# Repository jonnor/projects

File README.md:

Misc projects. Electronics, physical/mechanical, software.
3d-models, schematics, scripts.

# Introspectable computing

* [Agree.js](https://agreejs.org)
* [Finito](https://finitosm.org)

## Flow-based-programming

* [MicroFlo](https://microflo.org)
* [imgflo](https://imgflo.org)
* [MsgFlo](https://msgflo.org)
* [fbp-spec](https://github.com/flowbased/fbp-spec)
* [flowtrace](https://github.com/flowbased/flowtrace)

# Open hardware

* [TapeCore / TapeXY](./tapecore), an laserengraver and CNC motion platform
* [Idda](./idda-knitting-machine), a reverse-engineered ciruclar knitting machine.

# Digital fabrication tools

* [FreeCAD](./freecad) single-source /continious-integration
* [doctags](./doctags)

# Other interests

* [Bioplastic](./bioplastic)
* [Piezoelectricity](./piezo)
* [Automation](./automation)

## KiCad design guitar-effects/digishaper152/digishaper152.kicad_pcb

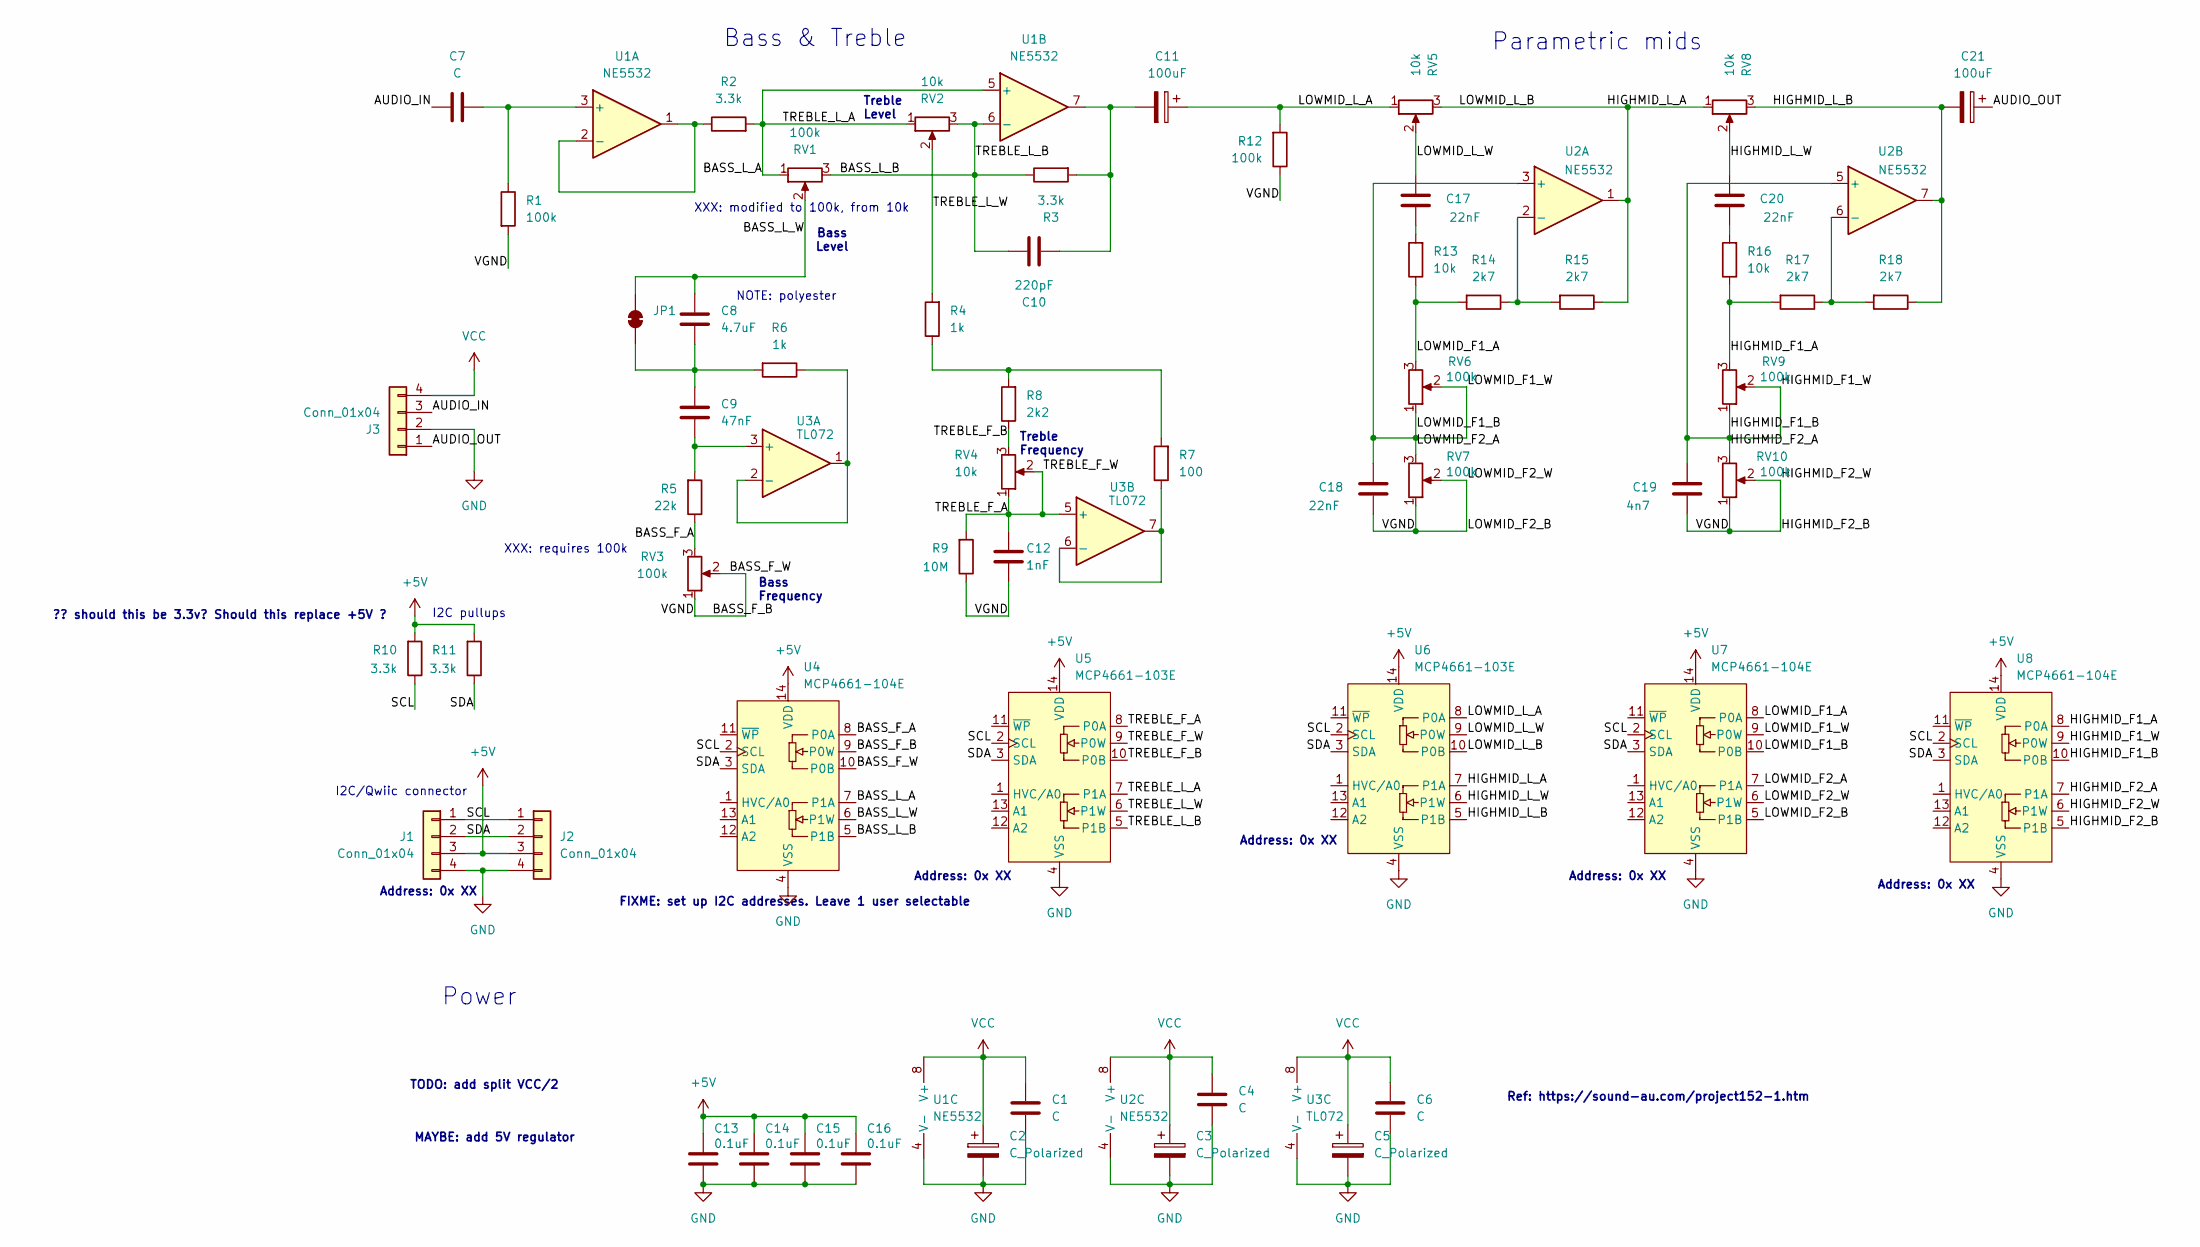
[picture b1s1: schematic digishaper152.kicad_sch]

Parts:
C1, C4, C6, C7: C; C_0805_2012Metric
C2, C3, C5: C_Polarized; C_0805_2012Metric
C8: 4.7uF; C_0805_2012Metric
C9: 47nF; C_0805_2012Metric
C10: 220pF; C_0805_2012Metric
C11, C21: 100uF; C_0805_2012Metric
C12: 1nF; C_0805_2012Metric
C13, C14, C15, C16: 0.1uF; C_0805_2012Metric
C17, C18, C20: 22nF; C_0805_2012Metric
C19: 4n7; C_0805_2012Metric
J1, J2: Conn_01x04; JST_SH_SM04B-SRSS-TB_1x04-1MP_P1.00mm_Horizontal
J3: Conn_01x04; PinHeader_1x04_P2.54mm_Vertical
JP1: SolderJumper_2_Bridged; SolderJumper-2_P1.3mm_Bridged_RoundedPad1.0x1.5mm
R1, R12: 100k; R_0805_2012Metric
R2, R3, R10, R11: 3.3k; R_0805_2012Metric
R4, R6: 1k; R_0805_2012Metric
R5: 22k; R_0805_2012Metric
R7: 100; R_0805_2012Metric
R8: 2k2; R_0805_2012Metric
R9: 10M; R_0805_2012Metric
R13, R16: 10k; R_0805_2012Metric
R14, R15, R17, R18: 2k7; R_0805_2012Metric
RV1, RV3, RV6, RV7, RV9, RV10: 100k; PinHeader_1x03_P1.27mm_Vertical
RV2, RV4, RV5, RV8: 10k; PinHeader_1x03_P1.27mm_Vertical
U1, U2: NE5532; SOIC-8_3.9x4.9mm_P1.27mm
U3: TL072; SOIC-8_3.9x4.9mm_P1.27mm
U4, U7, U8: MCP4661-104E; TSSOP-14_4.4x5mm_P0.65mm
U5, U6: MCP4661-103E; TSSOP-14_4.4x5mm_P0.65mm

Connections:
+5V: C13.1, C14.1, C15.1, C16.1, J1.3, J2.3, R10.2, R11.2, U4.14 (VDD), U5.14 (VDD), U6.14 (VDD), U7.14 (VDD), U8.14 (VDD)
/AUDIO_IN: C7.1, J3.3
/AUDIO_OUT: C21.1, J3.1
/BASS_F_A: R5.1, RV3.3, U4.8 (P0A)
/BASS_F_B: C12.1, C18.2, C19.2, R1.2, R9.1, R12.1, RV3.1, RV3.2, RV7.1, RV7.2, RV10.1, RV10.2, U4.9 (P0W), U4.10 (P0B), U7.5 (P1B), U7.6 (P1W), U8.5 (P1B), U8.6 (P1W)
/BASS_L_A: R2.2, RV1.1, RV2.1, U1.5 (+), U4.7 (P1A), U5.7 (P1A)
/BASS_L_B: C10.2, R3.1, RV1.3, RV2.3, U1.6 (-), U4.5 (P1B), U5.5 (P1B)
/BASS_L_W: C8.2, JP1.2 (B), RV1.2, U4.6 (P1W)
/HIGHMID_F1_A: R16.1, R17.2, RV9.3, U8.8 (P0A)
/HIGHMID_F1_B: C19.1, RV9.1, RV9.2, RV10.3, U2.5 (+), U8.7 (P1A), U8.9 (P0W), U8.10 (P0B)
/HIGHMID_L_A: R15.1, RV5.3, RV8.1, U2.1, U6.7 (P1A), U6.10 (P0B)
/HIGHMID_L_B: C21.2, R18.1, RV8.3, U2.7, U6.5 (P1B)
/HIGHMID_L_W: C20.1, RV8.2, U6.6 (P1W)
/LOWMID_F1_A: R13.1, R14.2, RV6.3, U7.8 (P0A)
/LOWMID_F1_B: C18.1, RV6.1, RV6.2, RV7.3, U2.3 (+), U7.7 (P1A), U7.9 (P0W), U7.10 (P0B)
/LOWMID_L_A: C11.1, R12.2, RV5.1, U6.8 (P0A)
/LOWMID_L_W: C17.1, RV5.2, U6.9 (P0W)
/SCL: J1.1, J2.1, R10.1, U4.2 (SCL), U5.2 (SCL), U6.2 (SCL), U7.2 (SCL), U8.2 (SCL)
/SDA: J1.2, J2.2, R11.1, U4.3 (SDA), U5.3 (SDA), U6.3 (SDA), U7.3 (SDA), U8.3 (SDA)
/TREBLE_F_A: C12.2, R9.2, RV4.1, RV4.2, U3.5 (+), U5.8 (P0A), U5.9 (P0W)
/TREBLE_F_B: R8.1, RV4.3, U5.10 (P0B)
/TREBLE_L_W: R4.2, RV2.2, U5.6 (P1W)
GND: C1.2, C2.2, C3.2, C4.2, C5.2, C6.2, C13.2, C14.2, C15.2, C16.2, J1.4, J2.4, J3.2, U1.4 (V-), U2.4 (V-), U3.4 (V-), U4.4 (VSS), U5.4 (VSS), U6.4 (VSS), U7.4 (VSS), U8.4 (VSS)
unnamed: C10.1, C11.2, R3.2, U1.7
unnamed: C17.2, R13.2
unnamed: C20.2, R16.2
unnamed: C8.1, C9.2, JP1.1 (A), R6.2
unnamed: R4.1, R7.2, R8.2
unnamed: C7.2, R1.1, U1.3 (+)
unnamed: R2.1, U1.1, U1.2 (-)
unnamed: R14.1, R15.2, U2.2 (-)
unnamed: R17.1, R18.2, U2.6 (-)
unnamed: C9.1, R5.2, U3.3 (+)
unnamed: R6.1, U3.1, U3.2 (-)
unnamed: R7.1, U3.6 (-), U3.7
VCC: C1.1, C2.1, C3.1, C4.1, C5.1, C6.1, J3.4, U1.8 (V+), U2.8 (V+), U3.8 (V+)

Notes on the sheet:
Bass & Treble
Address: 0x XX
MAYBE: add 5V regulator
XXX: modified to 100k, from 10k
Treble Level
FIXME: set up I2C addresses. Leave 1 user selectable
Parametric mids
Power
I2C pullups
XXX: requires 100k
Ref: https://sound-au.com/project152-1.htm
I2C/Qwiic connector
TODO: add split VCC/2
Bass Frequency
?? should this be 3.3v? Should this replace +5V ?
Bass Level
Treble Frequency
NOTE: polyester

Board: 2 copper layers, 61 parts (0 on the bottom side), 36 nets, no tracks yet.

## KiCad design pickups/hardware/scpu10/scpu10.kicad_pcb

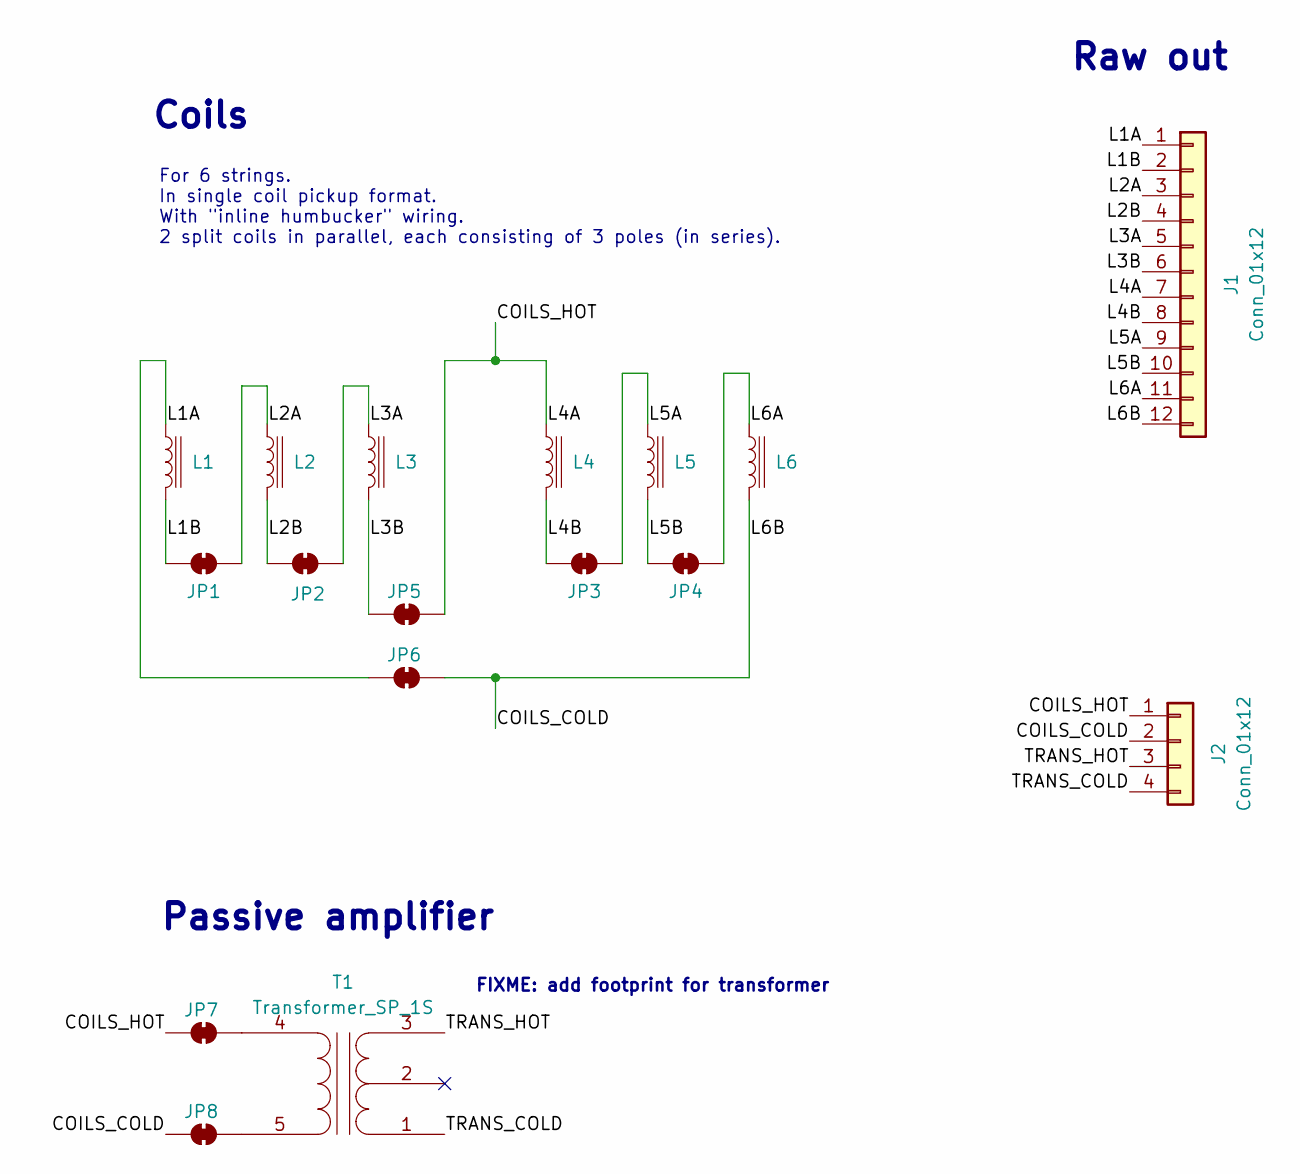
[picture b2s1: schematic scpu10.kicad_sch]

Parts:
J1: Conn_01x12; PinHeader_1x12_P2.54mm_Vertical
J2: Conn_01x12; PinHeader_1x04_P2.54mm_Vertical
JP1, JP2, JP3, JP4, JP5, JP6, JP7, JP8: SolderJumper_2_Bridged; SolderJumper-2_P1.3mm_Bridged_RoundedPad1.0x1.5mm
L1, L2, L3, L4, L5, L6: L_Iron; L_Radial_D8.7mm_P5.00mm_Fastron_07HCP
T1: Transformer_SP_1S

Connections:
/COILS_COLD: J1.12, J2.2, JP6.2 (B), JP8.1 (A), L6.2
/COILS_HOT: J1.7, J2.1, JP5.2 (B), JP7.1 (A), L4.1
/L1A: J1.1, JP6.1 (A), L1.1
/L1B: J1.2, JP1.1 (A), L1.2
/L2A: J1.3, JP1.2 (B), L2.1
/L2B: J1.4, JP2.1 (A), L2.2
/L3A: J1.5, JP2.2 (B), L3.1
/L3B: J1.6, JP5.1 (A), L3.2
/L4B: J1.8, JP3.1 (A), L4.2
/L5A: J1.9, JP3.2 (B), L5.1
/L5B: J1.10, JP4.1 (A), L5.2
/L6A: J1.11, JP4.2 (B), L6.1
/TRANS_COLD: J2.4, T1.1 (PR1)
/TRANS_HOT: J2.3, T1.3 (PR2)
unnamed: JP7.2 (B), T1.4 (S1)
unnamed: JP8.2 (B), T1.5 (S2)

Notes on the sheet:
For 6 strings. In single coil pickup format. With "inline humbucker" wiring. 2 split coils in parallel, each consisting of 3 poles (in series).
Raw out
FIXME: add footprint for transformer
Passive amplifier
Coils

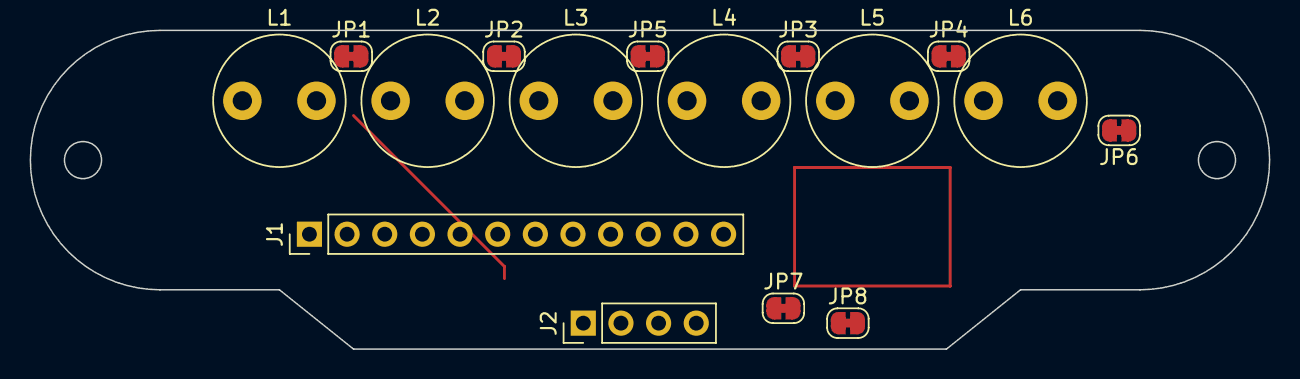
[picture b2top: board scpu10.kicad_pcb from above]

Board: 2 copper layers, 83.6 x 21.5 mm, 16 parts (0 on the bottom side), 12 nets.

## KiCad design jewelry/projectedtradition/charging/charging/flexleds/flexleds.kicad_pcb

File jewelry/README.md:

# Resin-based

Etsy.com. [Lots](https://www.etsy.com/no-en/search?q=epoxy+jewelry&explicit=1&page=3) of amazing looking products. Mostly rings,pendants.
Pure resin or resin+wood. 200-400 NOK. Sometimes glow-in-the-dark.
Resin 'stone' with wood base, silver ring inlay. 700-800 NOK.

Maybe silver + resin cast rings has good opportunity? Not found, might be able to push price up.

# Silver-based

Oxididation. Electroetching with laser-engraved masks?

# Gemstones

Small oval gemstones, 10-20 mm. [1](https://www.gemselect.com/group/gemselect.php?a=0&base_shape=Oval,Pear,Round&min_l=10.00&max_l=20.00&min_w=10.00&max_w=20.00&styles=Cabochon%27,%27Plain-Cut&price_asc=1&page=1)

# Rechargable

Power board for wearable or other battery powered electronics.

- Integrated charger for LIR coincell batteries.
- Integrated touch-controller for power on/off.
- Charging via USB 4pin magnetic cable.
- Fits LIR16xx,LIR20xx and LIR24xx directly.
- Board fits within 20 mm diameter, 2 mm height

## Top PCB

Projected. 3030 with touch on back

- 3030 LED on top
- 4 pin connector 1.0mm pitch
- Touch plate on the bottom.
Rounded rectangle
Keep below 12mm diameter?

## Tests

Tested charging. Seems to work as-intended.
Tested reverse-polarity protection. Works.

Tested attaching battery.
The solder joints may come out on lower side of PCB.
Can interfere with mounting. Should adapt bottom plate to accomodate.

Tested attaching cable for top PCB.
The purchased FFC just melts the backing material instantly. FAIL. Should use a Kapton-based instead.
It was possible to remove the thick spacers, add a Kapton+HT polyester layers, and melt away the plastic, and then solder this on.
However it remains quite tricky to do.
A jig to help with alignment would help.
Proper light and flux would also help.
Longer traces and wider pitch should be considered for next revision.

Need approx 45 mm FPC cable to get to top of dome.

Tested having an external copper piece for touch.
Using a resing printed dome, approx 1mm thick. Touching from outside.
With a single wire and 47 pF, did not react.
With alu foil of approx 10x10 mm and 47 pF, did not react.
With alu foil of approx 10x0 mm and C2 removed, reacts easily.
Need no or a small value for C2. Test 1 pF?

## TODO

Projected PCB rev 1 testing

- Add flat part to model dome, for LED PCB
- Assemble a complete piece
- Make stand functional
Thickness and tolerances on connector needs fixing
Orientation of cable outlet should be rotated 90degrees
- Test connector and charging, reliability/ease-of-use
- Try plugging the chargint through-hole.
See if one can use just SMT pads. Frees up a lot of board space for components.

Projected PCB rev 2 send

- Make LED/touch PCB for top.
Connections power,GND,touch
Include into main PCB project?
- Probably, use SMT pads for charging
- Maybe switch to 1.27mm solder tab FPC

Projected PCB rev 2 testing

- Make jig for holding PCBs and FPC cable for soldering
- Complete assembly. 3 units

## Next version

APA102 2020 strip
- ish 4 mm wide
- 4 pin connector. On LED side?
- space for 0603 capacitor
- at least 60mm length, for Atlantis earcuffs
- connector for chaining
- exposed pads between LEDs for ability to cut-to-length
- as close as possible. Ex 3 mm spacing 
can skip in software if not all are used

Insp. https://www.pcbway.com/project/shareproject/SK9822_APA102_LED_Breakout_board_array.html

Merge with "projected"

TODO:
- Test APA102 2020 / SK9822 at 3.6V power
Has been reported working ok.
https://forum.pjrc.com/threads/30020-Teensy-APA102-POV-Poi-Pixel-Poi-Build-Tutorial?p=84907&viewfull=1#post84907
- Integrate a microcontroller. ATtiny1616 ?
- Do touch control in microcontroller
- Support USB reconfiguration/programming over magnet connector
- Support APA102 style LEDs.
Put 1 on PCB, then to connector
VCC,GND,clk,data

## Notes
On two different magnetic USB cables, of same format. 4 pins
5V at tip, GND at base towards cable. Same.
However the magnets were oriented the other direction. South/North

## 2 pin inline

2 pin magnetic pogo pins
Many different sizes. Pin distances from 2 to 4mm
14 mm total length
https://www.aliexpress.com/item/4001134405952.html
https://www.aliexpress.com/item/33009498882.html
https://www.cletk.com/connector/high-class-2-pin-magnetic-charging-cable-for-smart-watch
https://www.aliexpress.com/item/4001065386444.html
https://www.aliexpress.com/item/4000209947392.html
https://www.aliexpress.com/item/4001149140826.html
https://www.aliexpress.com/item/1005002013444317.html

## Rotary magnetic

About 7.5 to 8.5 mm diameter

https://www.aliexpress.com/item/1005002177757313.html
https://www.aliexpress.com/item/4001135270257.html
https://www.aliexpress.com/item/4000109101082.html
https://www.aliexpress.com/item/4000109004581.html

## Parts 

Diode Shottky SOD323
https://www.digikey.com/en/products/filter/diodes-rectifiers-single/280?s=N4IgjCBcpgbFoDGUBmBDANgZwKYBoQB7KAbRAGYBOAJgBZ4DaAGJuiRlsSiAXQIAcALlBABlQQCcAlgDsA5iAC%2BBSvGghkkdNnxFSIZk3IB2ABwg%2BIISPHT5SggFpqCDVEkBXXcUhkArCAqFgLCkCAOII4B6prauAQ%2BZC6W1mFKyiBqoFIAJiKOYEzsVqHhBACOggCeIoWBINX8OCJoWMiKikA

PMOS SOT-223
https://www.digikey.com/en/products/filter/transistors-fets-mosfets-single/278?s=N4IgjCBcoGwAwyqAxlAZgQwDYGcCmANCAPZQDaIAzABwCsYclIAukQA4AuUIAyhwE4BLAHYBzEAF8iMMACYkIVJEy5CJcuBi0YsuCCKzDYGAE59IWTQAsc87NoB2KzCYHqT2lfOmwn7ybAHRGkTWV9zahsrWgjHLXMGOGiHBLgk2mpUpOp5IkSraky8uAyTM2LaUIg8hhgHGJrPMISrBDhq8BtaSoTHOAdXcD66BJNKJJSDNOodO0ofYIsHeuMWdi5IXgERcSlwWQCFJRV8IlJIClbaSiDzK5vJkFb2kwankqt6u4-ltZBObh8IRiSREAC08mgiigAgArmpzhQ3mZWP8NiBJHtEFDBAATbhghgdAGbcwARw4AE9uAxzFS2HhuBgcKgJBIgA

LIR1620 / LIR1632
LIR2032
LIR2450
Rainpro @ Aliexpress

LED driver. Linear regulator, low-dropout

BCR430U

## JST SUR 0.8 mm pitch connector

SM04B-SRSS-TB(LF)(SN) 
https://www.digikey.no/product-detail/no/jst-sales-america-inc/SM04B-SRSS-TB-LF-SN/455-1804-6-ND/1963508

There are now SUR connectors from JST also.
They have 0.8 mm pitch, and 1 mm height

https://www.digikey.com/en/products/detail/jst-sales-america-inc/SM04B-SURS-TF-LF-SN/7230518
https://www.digikey.com/en/products/detail/jst-sales-america-inc/A04SUR04SUR32W102A/9947438

https://www.aliexpress.com/item/32835280612.html?spm=a2g0o.cart.0.0.44853c0032a3Bk&mp=1
https://www.aliexpress.com/item/32834920580.html?spm=a2g0o.cart.0.0.44853c0032a3Bk&mp=1
https://www.aliexpress.com/item/4001089049756.html?spm=a2g0o.cart.0.0.44853c0032a3Bk&mp=1
https://www.aliexpress.com/item/4001089049756.html?spm=a2g0o.cart.0.0.44853c0032a3Bk&mp=1

FPC connector
https://www.digikey.com/en/products/detail/te-connectivity-amp-connectors/1734839-5/1860461

BCR430U

# Watch
Watch case 42 mm 43mm 
For movement ST36 ETA6497 ETA6498 P212
transparent back

https://www.aliexpress.com/item/4000229421123.html
https://www.aliexpress.com/item/4000689159663.html
https://www.aliexpress.com/item/32907052343.html

# Integrated electronics

## Structures

* Necklace, 2 parts on front connected with a tube. LED (and switch?) in one, battery in other.
* Pendant small. Eg with lit gemstone. LED and switch IC PCB underneath gemstone. Battery in/on clasp. 
* Pendant big. All electronics, incl battery, in pendant.

## Tested

Using bent copper wires on PCB for coincell battery holder.
GND as wire loop lying on PCB, VBAT as a loop standing out from board, that coincell slides underneath. Works nicely.
A jig could help bending correct wires before placing.

## Lights in motion

Animation ideas

* Subtle glow
* Glitter/sparkle. Random high-intensity bursts, alternating positions
* Together<->apart / center<->sides. 
* Swipe across. Random triggered, varying intensity
* Tick-tock. Move back/forward in a way that suggests clock motion

## Interactivity

* "touch me". Touch. Proximity. Gestures. Capacitive sensing.
* "move me". Motion. Angle. Accelerometer
* "I hear you". Sound. Music, wearer talking. Microphone.
* "I feel you". Body state. Temperature, breathing, heartbeat.
* "get close to me". Distance

Modulate intensity using touch proximity?

Accelerometers are available with `<10uA` consumption in low power mode.
I2C communication and configurable interrupts. Ex: LIS3DE, MMA8653FC 

# Learnings

Minimum hole size in cardboard. Vector: 0.5mm

# Rev2

* Total size `<40mm` diam, `<15 mm` height. Domed top. PCB 20mm diam, `<3mm` component height.
* LiPo battery, integrated charger. LIR2450-LIR2016
* Pogopin connector for charging
* TPP223 touch controller
* 3030 or 3535 white LED. Low-profile, 1mm. Low voltage? 3V
* LED constant-current driver

0.6mm PCB is OK priced on PCBWay. 0.4 and 0.2mm twice the price.
10mA on time.

FPC connector.
https://www.digikey.com/products/en/connectors-interconnects/ffc-fpc-flat-flexible-connectors/399?FV=fff40016%2Cfff80421%2C1600018%2C1600006%2C1b4c0008%2Cffe0018f%2Cfffc0017%2Cfffc0384&quantity=20&ColumnSort=1000011&page=2&stock=1&nstock=1&pageSize=25

100mAh, 10uA => 1 year.

LEDs

https://www.digikey.com/products/en/optoelectronics/led-lighting-white/124?FV=7%7C2%2C37%7C421162%2C319%7C133405%2C319%7C134015%2C319%7C134067%2C319%7C134280%2C319%7C134430%2C319%7C134479%2C319%7C134532%2C319%7C134768%2C319%7C135281%2C319%7C135361%2C319%7C135451%2C319%7C135630%2C319%7C135739%2C319%7C136170%2C319%7C136604%2C319%7C136643%2C319%7C136960%2C319%7C137263%2C319%7C137391%2C319%7C202627%2C319%7C202630%2C1500%7C4992%2C1500%7C5027%2C1500%7C5068%2C1500%7C5221%2C1500%7C5295%2C1500%7C5576%2C1500%7C5588%2C1500%7C5744%2C1500%7C5802%2C1500%7C5803%2C1500%7C5812%2C1500%7C5916%2C1500%7C5964%2C1500%7C6031%2C1500%7C6094%2C1500%7C6506%2C-8%7C124%2C1291%7C182983%2C1291%7C193429&quantity=10&ColumnSort=1000011&page=2&stock=1&nstock=1&pageSize=25

# TODO

* Make bottom PCB.
* Make LED PCB. Touch sensor electrode also?

Dock

* Fabricate a PCB for dock
* Make docking station mechanics

Later

* Move to separate repository

## USB DFU

USB DFU on STM32L432 and STM32L433
not conforming to spec?
https://community.st.com/s/question/0D50X00009XkfyUSAR/usb-dfu-on-stm32l432-and-stm32l433
Issue seems fixed in latest st-util?
https://sourceforge.net/p/dfu-util/tickets/40/

User-mode bootloader
https://github.com/nichtgedacht/L433CCTx-bootloader

# Ideas

Practical sizes

* Test a CR coincell holder inline with the PCB instead of on the back.
U-shape opening on one side. Wires on each side for GND/VBAT.
Reduces thickness by board+component height, approx 3 mm.
* Test using silver chains as conductor to battery.
Challenge: Has to be safe to have them touching, avoid shorts.
Current limiter. Active, passive resistor.

Consumer friendliness

* Ensure easy to put in battery correctly.
* Ensure that putting battery incorrectly does not cause damage?
* Maybe allow to adjust brightness. Touch-and-hold during startup?

Capacitive touch on/off

* Test have a hole/slit in housing, where a metallic piece/wire rests as the electrode.
Jewelry connected to GND.
* Test having a wire antenna sticking out towards front of rosebud.
With high sensitivity, can one switch using a gesture?

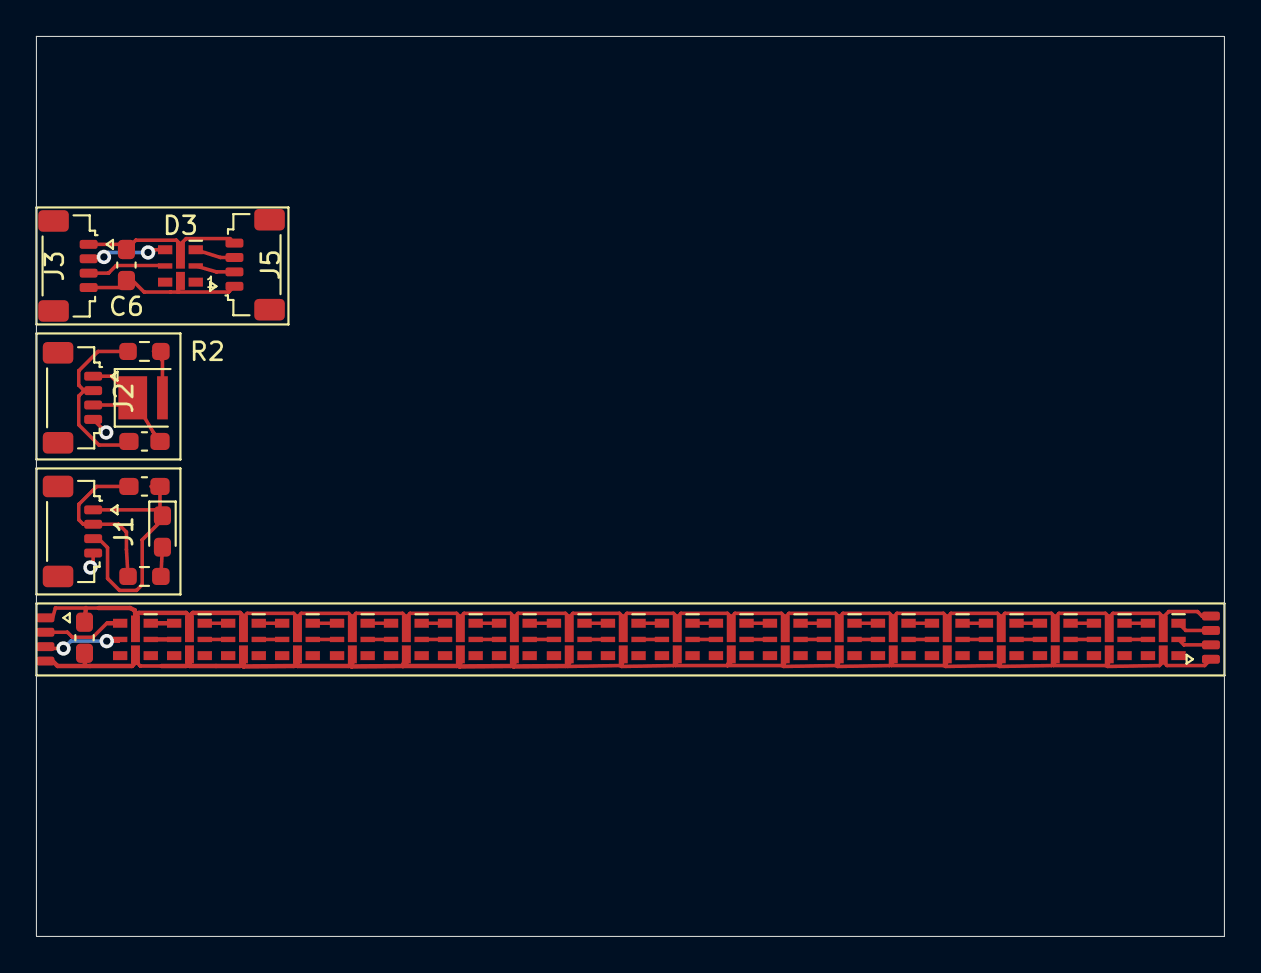
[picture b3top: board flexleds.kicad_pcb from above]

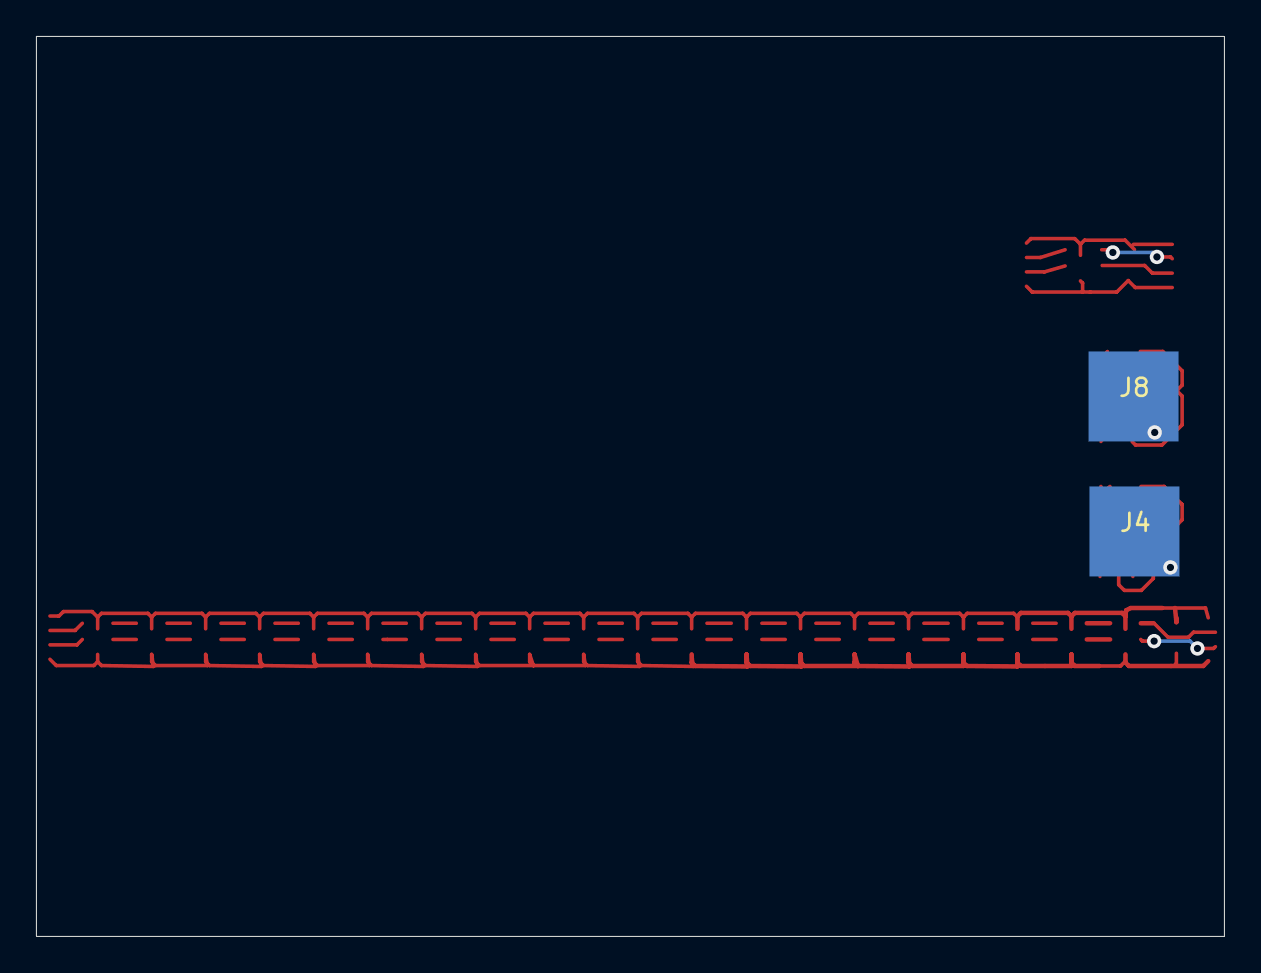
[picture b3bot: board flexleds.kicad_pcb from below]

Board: 2 copper layers, 66.0 x 50.0 mm, 37 parts (2 on the bottom side), 56 nets.

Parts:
C1, C3, C6, C7: C; C_0603_1608Metric_Pad1.08x0.95mm_HandSolder
D1: LED; LED_0603_1608Metric_Pad1.05x0.95mm_HandSolder
D2: LED; LED_Cree-J3030
D3, D4, D5, D6, D7, D8, D9, D10, D11, D12, D13, D14, D15, D16, D17, D18, D19, D20, D21, D22, D23: APA102-2020; LED-APA102-2020-midpower
J1, J2, J3, J5: Conn_01x04; JST_SUR_SM04B-SURS-TF_1x04-1MP_P0.80mm_Horizontal
J4, J8: Conn_01x01; touchpad
J6, J7: Conn_01x04; JST_SUR_SM04B-SURS-TF_1x04-1MP_P0.80mm_Horizontal_cut
R1, R2: R; R_0603_1608Metric_Pad0.98x0.95mm_HandSolder

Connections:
/0603_led: C1.1, J1.2, R1.1
/0603_touch: J1.4, J4.1
/3030_led: C3.1, J2.2, R2.1
/3030_touch: J2.4, J8.1
GND: C3.2, C6.2, C7.2, D2.1, D3.6, D4.6, D5.6, D6.6, D7.6, D8.6, D9.6, D10.6, D11.6, D12.6, D13.6, D14.6, D15.6, D16.6, D17.6, D18.6, D19.6, D20.6, D21.6, D22.6, D23.6, J2.1, J2.3, J3.1, J5.4, J6.1, J7.4
unnamed: C1.2, D1.1, J1.1, J1.3
unnamed: C6.1, D3.1, J3.4, J5.1
unnamed: C7.1, D4.1, D5.1, D6.1, D7.1, D8.1, D9.1, D10.1, D11.1, D12.1, D13.1, D14.1, D15.1, D16.1, D17.1, D18.1, D19.1, D20.1, D21.1, D22.1, D23.1, J6.4, J7.1
unnamed: D1.2, R1.2
unnamed: D2.2, R2.2
unnamed: D3.2, J5.2
unnamed: D3.3, J5.3
unnamed: D3.4, J3.2
unnamed: D3.5, J3.3
unnamed: D4.2, D5.5
unnamed: D4.3, D5.4
unnamed: D4.4, J6.2
unnamed: D4.5, J6.3
unnamed: D5.2, D6.5
unnamed: D5.3, D6.4
unnamed: D6.2, D7.5
unnamed: D6.3, D7.4
unnamed: D7.2, D8.5
unnamed: D7.3, D8.4
unnamed: D8.2, D9.5
unnamed: D8.3, D9.4
unnamed: D10.2, D11.5
unnamed: D10.3, D11.4
unnamed: D9.3, D10.4
unnamed: D9.2, D10.5
unnamed: D11.2, D12.5
unnamed: D11.3, D12.4
unnamed: D12.2, D13.5
unnamed: D12.3, D13.4
unnamed: D13.2, D14.5
unnamed: D13.3, D14.4
unnamed: D14.2, D15.5
unnamed: D14.3, D15.4
unnamed: D15.2, D16.5
unnamed: D15.3, D16.4
unnamed: D16.2, D17.5
unnamed: D16.3, D17.4
unnamed: D17.2, D18.5
unnamed: D17.3, D18.4
unnamed: D18.2, D19.5
unnamed: D18.3, D19.4
unnamed: D19.2, D20.5
unnamed: D19.3, D20.4
unnamed: D20.2, D21.5
unnamed: D20.3, D21.4
unnamed: D21.2, D22.5
unnamed: D21.3, D22.4
unnamed: D22.2, D23.5
unnamed: D22.3, D23.4
unnamed: D23.2, J7.2
unnamed: D23.3, J7.3

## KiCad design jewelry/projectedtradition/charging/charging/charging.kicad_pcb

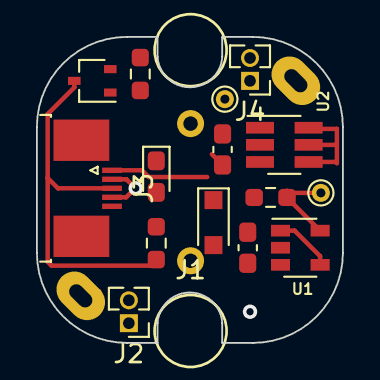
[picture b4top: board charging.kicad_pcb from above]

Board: 2 copper layers, 17.0 x 17.0 mm, 17 parts (0 on the bottom side), 9 nets.

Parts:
BT1: Battery_Cell; batt-lir-2012
C1, C2: C; C_0603_1608Metric_Pad1.08x0.95mm_HandSolder
D1: D_Schottky; D_SOD-323_HandSoldering
D2: LED; LED_0603_1608Metric_Pad1.05x0.95mm_HandSolder
J1: Conn_01x04; magconnect4-poweronly
J2, J4: Conn_01x02; PinHeader_1x02_P1.27mm_Vertical
J3: Conn_01x04; TE_0-1734839-5_1x05-1MP_P0.5mm_Horizontal
Q1: PMOS SOT223; SOT-323_SC-70
R1, R2: 22k; R_0603_1608Metric_Pad0.98x0.95mm_HandSolder
R3: 1k2; R_0603_1608Metric_Pad0.98x0.95mm_HandSolder
TP1, TP2: TestPoint; TestPoint_THTPad_D1.0mm_Drill0.5mm
U1: MCP73812T-420I-OT; SOT-23-5
U2: TPP223-BA6; SOT-23-6_Handsoldering

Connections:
+BATT: BT1.1, J2.1, J4.1, Q1.2, R2.1, U1.3, U2.4, U2.5, U2.6
-BATT: BT1.2, C1.2, C2.2, D2.1, J1.4, J2.2, J3.2, J3.4, R1.2, U1.2, U2.2
/POWER_EN: Q1.1, R2.2, TP2.1, U2.1
/POWER_OUT: J3.3, J4.2, Q1.3, R3.1
/TOUCH_SENSE: C2.1, J3.1, U2.3
unnamed: D1.2, J1.1
unnamed: D2.2, R3.2
unnamed: R1.1, TP1.1, U1.5
VBUS: C1.1, D1.1, U1.1, U1.4

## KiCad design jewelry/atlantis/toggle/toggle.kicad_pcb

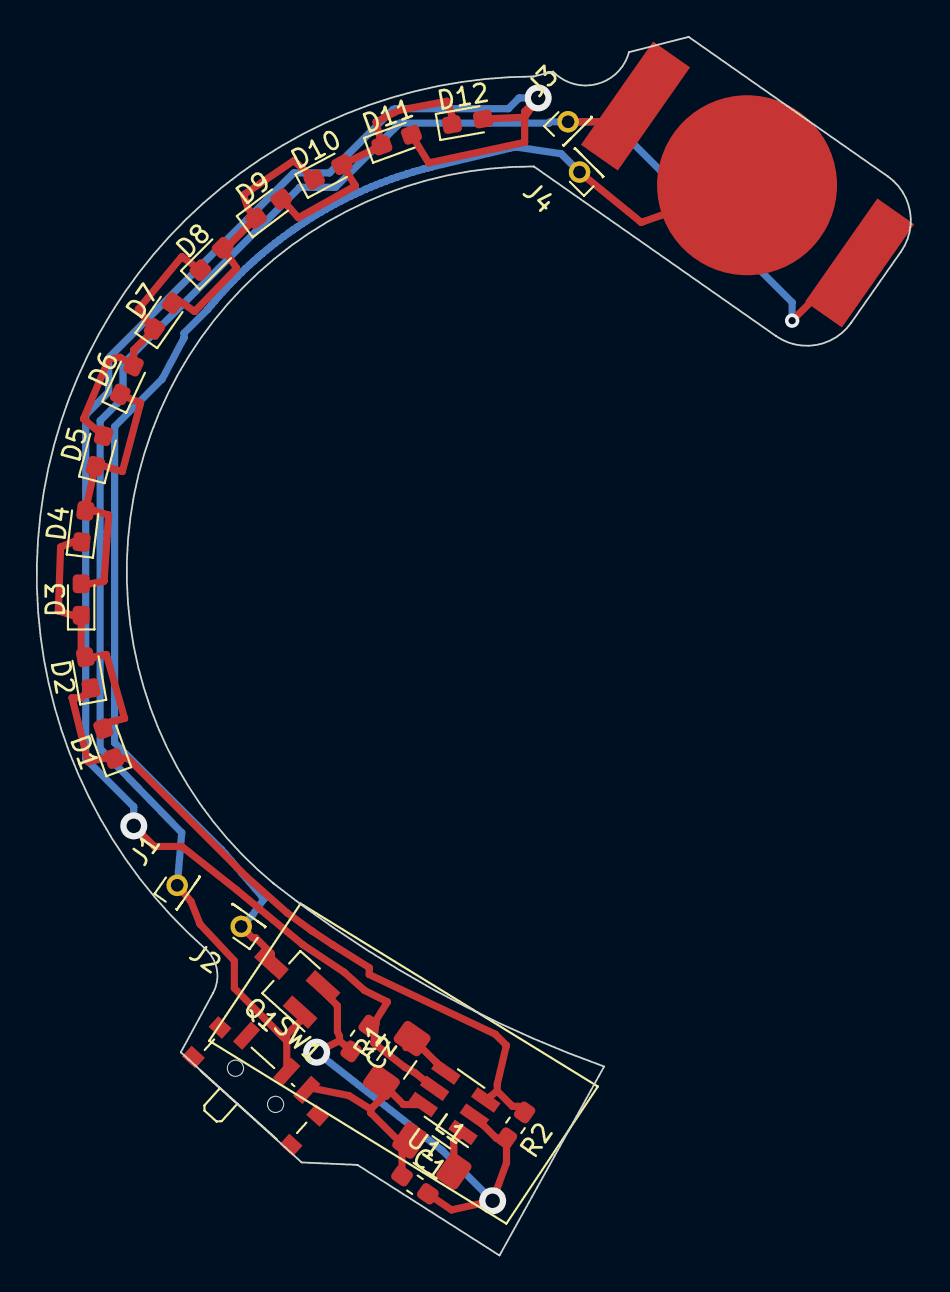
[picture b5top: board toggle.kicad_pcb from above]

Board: 2 copper layers, 48.5 x 67.7 mm, 25 parts (0 on the bottom side), 13 nets.

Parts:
BT1: CR1216; Battery_CR1225
C1, C2: 1uF; C_0603_1608Metric_Pad1.05x0.95mm_HandSolder
D1, D2, D3, D4, D5, D6, D7, D8, D9, D10, D11, D12: LED; LED_0603_1608Metric_Pad1.05x0.95mm_HandSolder
J1, J2, J3, J4: Conn_01x01; PinHeader
L1: L; L_1206_3216Metric_Pad1.42x1.75mm_HandSolder
Q1: BSS138L; SOT-23_Handsoldering
R1: 100k; R_1206_3216Metric_Pad1.42x1.75mm_HandSolder
R2: 220R; R_0603_1608Metric_Pad1.05x0.95mm_HandSolder
SW1: SW_SPDT; SW_SPDT_PCM12
U1: AP3019A; SOT-223-6-extraspace

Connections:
/BATT+: BT1.1, J1.1, J3.1, Q1.1, SW1.2
/BATT-: BT1.2, J2.1, J4.1, Q1.3
/LED+: C2.1, D11.2, D12.2, U1.5
/LED-: D1.1, D2.1, R2.1, U1.3
GND: C1.2, C2.2, Q1.2, R2.2, U1.2
unnamed: D1.2, D2.2, D3.1, D4.1
unnamed: D3.2, D4.2, D5.1, D6.1
unnamed: D5.2, D6.2, D7.1, D8.1
unnamed: D7.2, D8.2, D9.1, D10.1
unnamed: D9.2, D10.2, D11.1, D12.1
unnamed: L1.2, U1.1
unnamed: R1.2, U1.4
VCC: C1.1, L1.1, R1.1, SW1.3, U1.6

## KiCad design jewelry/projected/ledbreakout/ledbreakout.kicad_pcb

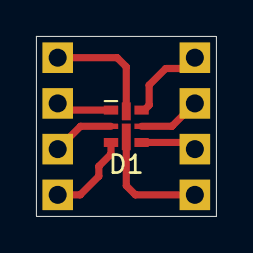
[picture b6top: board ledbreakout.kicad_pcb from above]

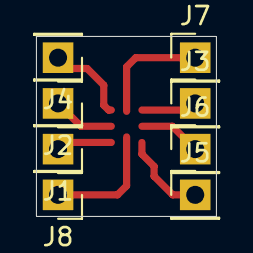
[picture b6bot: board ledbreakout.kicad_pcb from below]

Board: 2 copper layers, 10.0 x 10.0 mm, 9 parts (8 on the bottom side), 6 nets.

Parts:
D1: APA102-2020; LED-APA102-2020
J1, J2, J3, J4, J5, J6, J7, J8: Conn_01x01; PinHeader_1x01_P2.54mm_Vertical

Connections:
GND: D1.6, J4.1, J8.1
unnamed: D1.2, J6.1
unnamed: D1.3, J5.1
unnamed: D1.4, J1.1
unnamed: D1.5, J2.1
VCC: D1.1, J3.1, J7.1

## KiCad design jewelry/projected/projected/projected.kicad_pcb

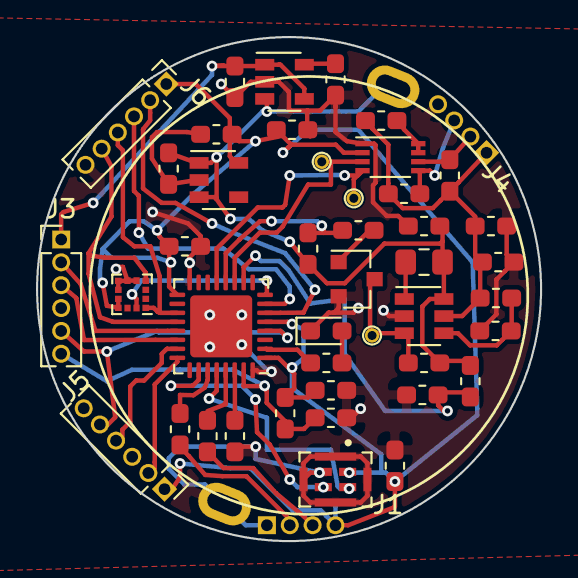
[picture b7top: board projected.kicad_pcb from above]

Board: 2 copper layers, 28.0 x 28.0 mm, 46 parts (0 on the bottom side), 38 nets.

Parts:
BT1: LIR2450; LIR2450-horizontal-pins
C1: C; C_0603_1608Metric_Pad1.05x0.95mm_HandSolder
C2, C3, C4, C5, C6, C7, C8, C9, C10, C11: 1uF; C_0603_1608Metric_Pad1.05x0.95mm_HandSolder
D2: LED; LED_0603_1608Metric_Pad1.05x0.95mm_HandSolder
J1: TOUCH; Pins_1x04_P1.27mm
J3: DOCK; Pins_1x06_P1.27mm
J4: Leds; Pins_1x04_P1.27mm
J5: SWD; Pins_1x06_P1.27mm
J6: EXT; Pins_1x06_P1.27mm
L1: 4.7uH; L_0805_2012Metric_Pad1.15x1.40mm_HandSolder
Q1: BC847CL; SOT-23
R1, R2: 1k; R_0603_1608Metric_Pad1.05x0.95mm_HandSolder
R3, R8, R9: R; R_0603_1608Metric_Pad1.05x0.95mm_HandSolder
R4: 22k; R_0603_1608Metric_Pad1.05x0.95mm_HandSolder
R5, R6: 10k; R_0603_1608Metric_Pad1.05x0.95mm_HandSolder
R7, R12: 4k7; R_0603_1608Metric_Pad1.05x0.95mm_HandSolder
R10: 330k; R_0603_1608Metric_Pad1.05x0.95mm_HandSolder
R11, R13, R14: 100k; R_0603_1608Metric_Pad1.05x0.95mm_HandSolder
R15, R16: 3k3; R_0603_1608Metric_Pad1.05x0.95mm_HandSolder
TP1: TestPoint; TestPoint_Mini
TP2: LED_CLK; TestPoint_Mini
TP3: LED_DATA; TestPoint_Mini
U1: STM32L432KBU6; QFN-32-1EP_5x5mm_P0.5mm_EP3.45x3.45mm
U2: MCP73812T-420I-OT; SOT-23-5
U3: PCA9306DCUR; VSSOP-8_2.3x2mm_P0.5mm
U4: MCP1640BT-I/CHY‎; SOT-23-6
U5: TPS7A0533PDBVT; SOT-23-5
U6: LIS2DE12TR‎; LGA-12_2x2mm_P0.5mm
U7: MIC; XDCR_CMM-4030DT-26154-TR

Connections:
+5V: C5.1, C9.1, J4.1, R10.1, R14.2, R15.2, R16.2, U4.5
+BATT: BT1.1, C4.1, C7.1, L1.1, R7.1, R8.2, R13.1, U2.3, U4.6, U5.1, U5.3
/ACCEL_INT: U1.8, U6.12
/ANALOG+: J6.2, U1.6
/ANALOG-: J6.3, U1.7
/BATT_SENSE: R8.1, R9.2, U1.10
/BOOT: J3.6, R5.2, R6.1, U1.31
/I2C_SCL: J6.4, U1.19, U6.1
/I2C_SDA: J6.5, U1.20, U6.4
/LED_CLK: TP2.1, U1.11, U3.3
/LED_CLK_5V: J4.2, R15.1, U3.6
/LED_DATA: TP3.1, U1.13, U3.4
/LED_DATA_5V: J4.3, R16.1, U3.5
/LED_ENABLE: R7.2, R12.2, U1.12
/LED_STATUS: R3.1, U1.2
/RESET: J3.5, J5.5, U1.4
/SAI_SCK: U1.26, U7.2
/SAI_SD: U1.28, U7.1
/SWD_CLK: J5.2, U1.24
/SWD_IO: J5.4, U1.23
/TOUCH_1: R1.2, U1.27
/TOUCH_2: R2.2, U1.29
/TOUCH_CS: C1.1, U1.30
/USB_D+: J3.3, U1.22
/USB_D-: J3.2, U1.21
GND: BT1.2, C1.2, C2.2, C3.2, C4.2, C5.2, C6.2, C9.2, C10.2, C11.2, D2.1, J1.1, J3.4, J4.4, J5.3, J6.6, Q1.2, R4.2, R6.2, R9.1, R11.2, U1.16, U1.32, U1.33, U2.2, U3.1, U4.2, U6.5, U6.6, U6.7, U6.8, U7.3, U7.5, U7.6, U7.7, U7.8
unnamed: C7.2, C8.2, U5.2
unnamed: D2.2, R3.2
unnamed: J1.2, R1.1
unnamed: J1.3, R2.1
unnamed: L1.2, U4.1
unnamed: Q1.1, R12.1
unnamed: Q1.3, R13.2, TP1.1, U4.3
unnamed: R4.1, U2.5
unnamed: R10.2, R11.1, U4.4
unnamed: R14.1, U3.7, U3.8
VBUS: C2.1, J3.1, U2.1, U2.4
VCC: C3.1, C6.1, C8.1, C10.1, C11.1, J1.4, J5.1, J6.1, R5.1, U1.1, U1.5, U1.17, U3.2, U5.5, U6.9, U6.10, U7.4

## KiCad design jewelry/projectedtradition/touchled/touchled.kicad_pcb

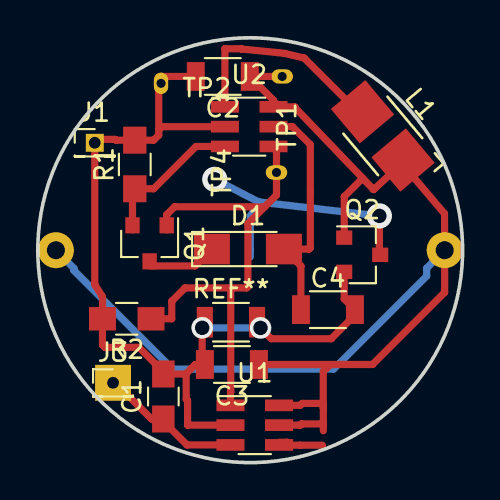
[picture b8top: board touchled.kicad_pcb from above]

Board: 2 copper layers, 23.6 x 23.6 mm, 18 parts (1 on the bottom side), 9 nets.

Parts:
BT1: CR2032; BK-913
C1: 47pF; C_0805_HandSoldering
C2, C3, C4: 1uF; C_1206
D1: LED; LED_1206_HandSoldering
J1: SENSEGND; Pin_Header_Straight_1x01_Pitch1.27mm
J3: SENSE; Pin_Header_Straight_1x01_Pitch1.27mm
L1: L; Inductor_1212
Q1, Q2: BSS138L; SOT-23
R1: 12R; R_0805_HandSoldering
R2: 100k; R_0805_HandSoldering
TP1: VDD; progpin
TP2: GND; progpin
TP4: ON; progpin
U1: TPP223-BA6; SOT-223-6-extraspace
U2: AP3019A; SOT-223-6-extraspace

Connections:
/LED+: C4.1, D1.2, U2.5
/LED-: D1.1, Q1.3
/sensor: C1.1, J3.1, U1.3
GND: C1.2, C2.2, C3.2, C4.2, J1.1, Q2.2, R1.2, R2.2, TP2.1, U1.2, U2.2
unnamed: BT1.2, Q2.3
unnamed: L1.2, U2.1
unnamed: Q1.2, R1.1, U2.3
VDD: BT1.1, C2.1, C3.1, L1.1, Q2.1, TP1.1, U1.5, U1.6, U2.6
touchon: Q1.1, R2.1, TP4.1, U1.1, U2.4
